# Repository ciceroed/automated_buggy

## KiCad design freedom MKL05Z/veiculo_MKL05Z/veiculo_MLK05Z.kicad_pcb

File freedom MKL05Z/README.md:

# Interface shield

This shield was adapted to connect MKL05Z pins to the car's power board. Go to [Power Board](hhttps://github.com/xtarke/automated_buggy/tree/master/power_board) for more hardware information.

## Analog pins

| Analog input  | KL05Z pin  | Board label  | Signal |
| ------------- | -------- | ------------ | ------ |
| ADC0          | PTA8       |   ADC0       | Bat0   |
| ADC1          | PTB9       |   ADC1       | Bat1   |
| ADC2          | PTB8       |   ADC2       | Ampop1 |
| ADC3          | PTA0       |   ADC3       | Ampop2 |

## Ultrasonic sensor

| MK05Z Pin | Signal|
| ------- | ------|
| PTB10       | Echo0 |
| PTB7       | Trig0 |
| PTA11       | Echo1 |
| PTA10       | Trig1 |

## Motors

|MK05Z Pin | Signal|  Board label |
| ---------- | ------| ------------ |
| PTB6          | PWM1  |  M1          |
| PTA12          | PWM1N |  M1N         |
| PTA5         | PWM2  |  M2          |
| PTB5          | PWM2N |  M2N         |

## Speed econder

| MKL05Z Pin | Signal |  Board label |
| ----------- | ------ | ------------ |
| PTB0          | D0     | ENC0         |
| PTA6          | D1     | ENC1         |

## Optic sensor

| MKL05Z Pin | Signal | Board label |
| ----------- | ------ | ----------- |
| PTB4          | R_TCRT | R DIR       |
| PTB3        | L_TCRT | L ESQ       |

## UART

| MKL05Z Pin | Signal |
| ------- | ------ |
| TX      | TX     |
| RX      | RX     |

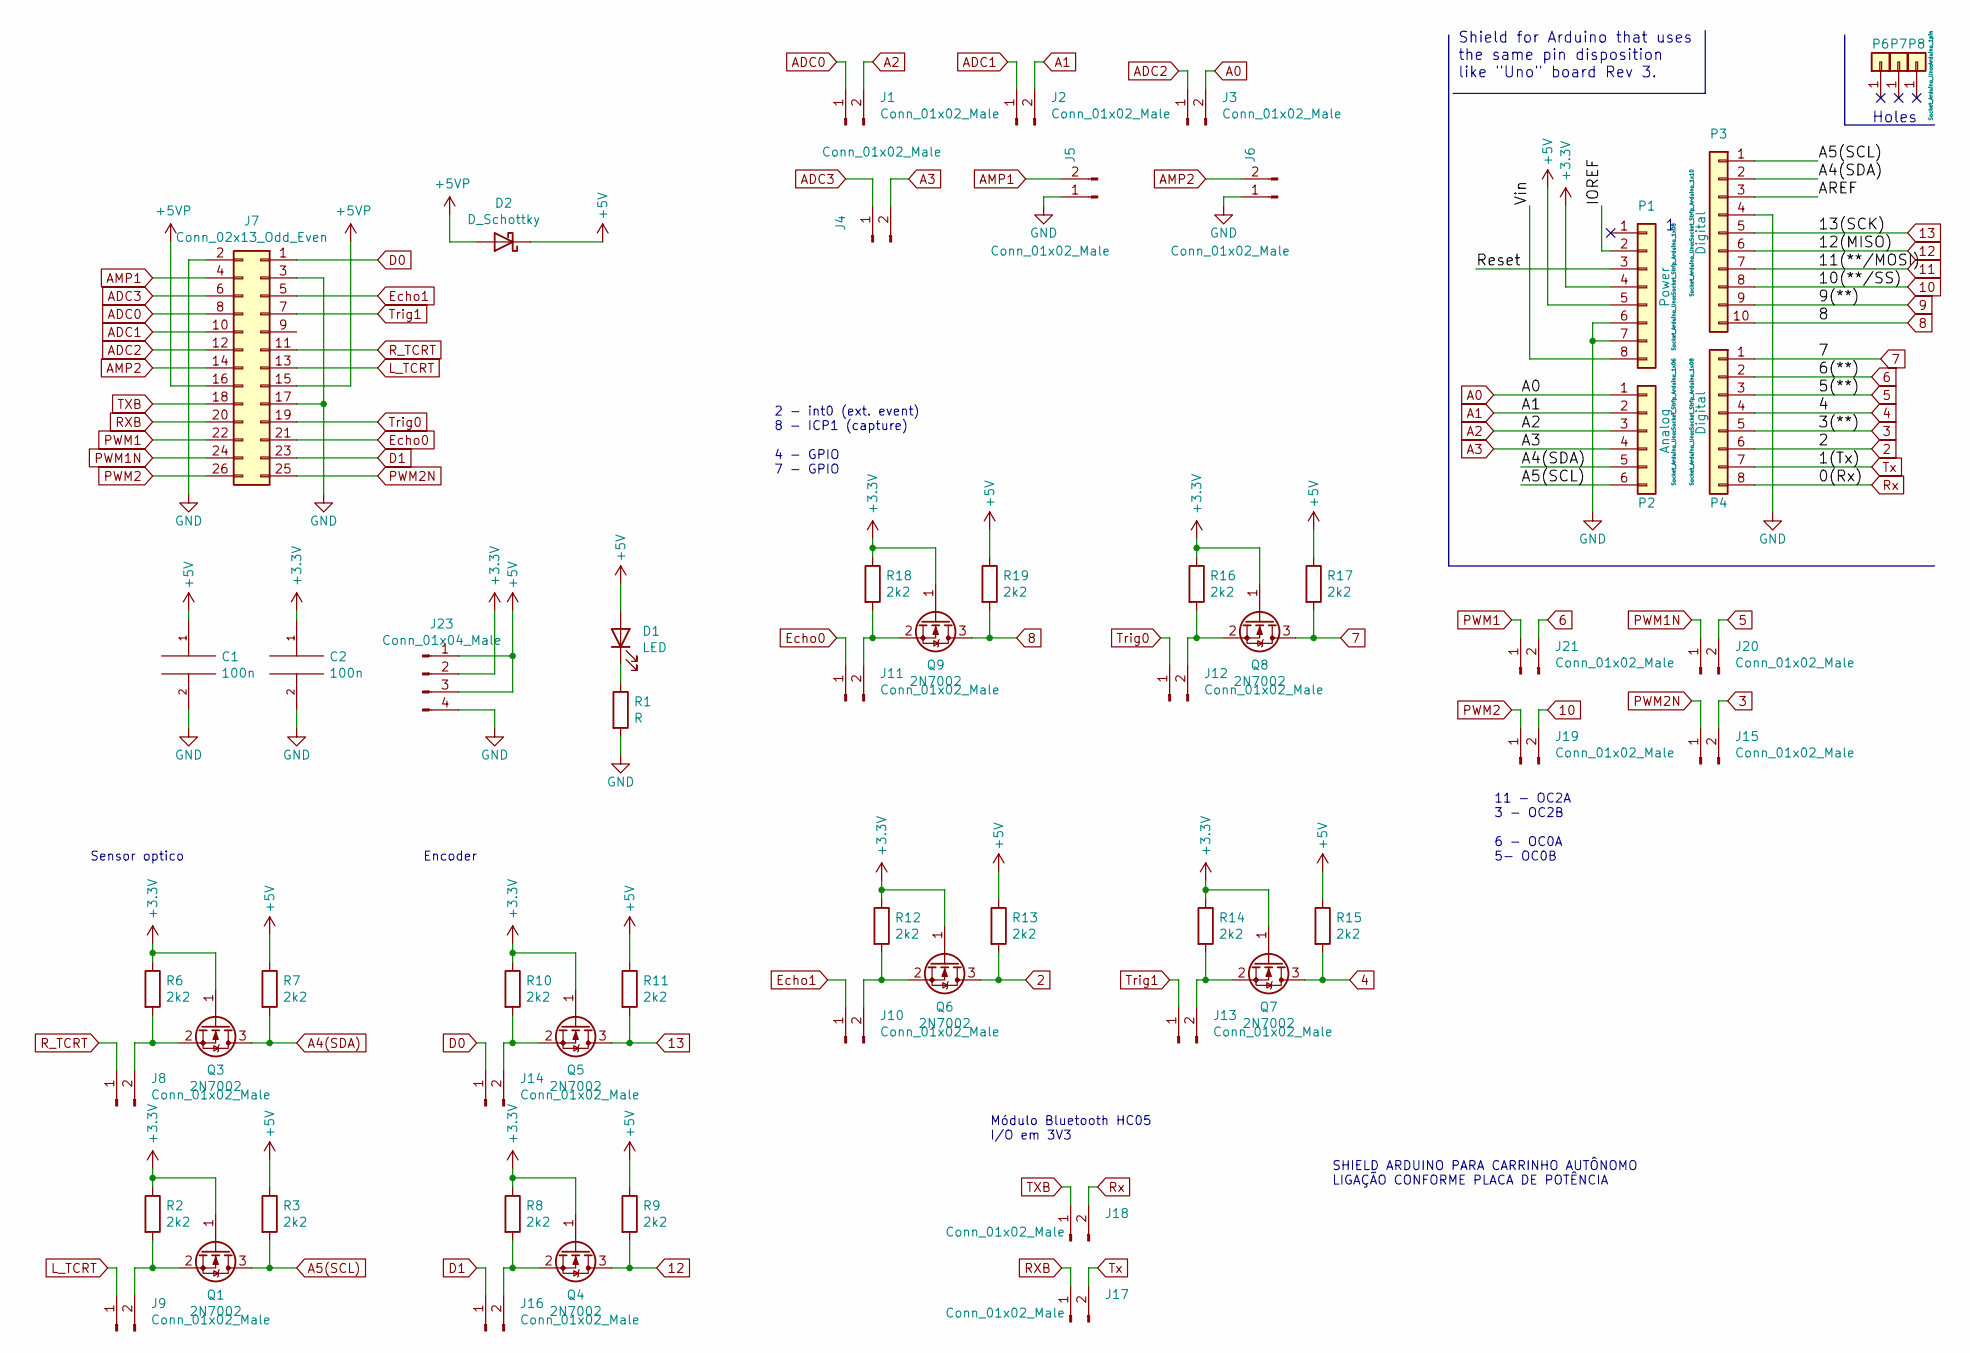
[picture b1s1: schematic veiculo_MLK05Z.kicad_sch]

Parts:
C1, C2: 100n; C_0805_2012Metric_Pad1.15x1.40mm_HandSolder
D1: LED; LED_0805_2012Metric
D2: D_Schottky; D_SMB
J1, J2, J3, J4, J5, J6, J8, J9, J10, J11, J12, J13, J14, J15, J16, J17, J18, J19, J20, J21: Conn_01x02_Male; PinHeader_1x02_P2.54mm_Vertical
J7: Conn_02x13_Odd_Even; IDC-Header_2x13_P2.54mm_Vertical
J23: Conn_01x04_Male; PinHeader_1x04_P2.54mm_Vertical
P1: Power; Socket_Strip_Arduino_1x08
P2: Analog; Socket_Strip_Arduino_1x06
P3: Digital; Socket_Strip_Arduino_1x10
P4: Digital; Socket_Strip_Arduino_1x08
P6, P7, P8: CONN_01X01; Arduino_1pin
Q1, Q3, Q4, Q5, Q6, Q7, Q8, Q9: 2N7002; SOT-23
R1: R; R_0805_2012Metric
R2, R3, R6, R7, R8, R9, R10, R11, R12, R13, R14, R15, R16, R17, R18, R19: 2k2; R_0805_2012Metric

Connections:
2: P4.6, Q6.3 (D), R13.2
3: J15.2, P4.5
4: P4.4, Q7.3 (D), R15.2
5: J20.2, P4.3
6: J21.2, P4.2
7: P4.1, Q8.3 (D), R17.2
8: P3.10, Q9.3 (D), R19.2
9: P3.9
10: J19.2, P3.8
11: P3.7
12: P3.6, Q4.3 (D), R9.2
13: P3.5, Q5.3 (D), R11.2
+3.3V: C2.1, J23.2, P1.4, Q1.1 (G), Q3.1 (G), Q4.1 (G), Q5.1 (G), Q6.1 (G), Q7.1 (G), Q8.1 (G), Q9.1 (G), R2.1, R6.1, R8.1, R10.1, R12.1, R14.1, R16.1, R18.1
+5V: C1.1, D1.2 (A), D2.1 (K), J23.1, J23.3, P1.5, R3.1, R7.1, R9.1, R11.1, R13.1, R15.1, R17.1, R19.1
+5VP: D2.2 (A), J7.15, J7.16
/AREF: P3.3
/IOREF: P1.2
/Reset: P1.3
/Vin: P1.8
A0: J3.2, P2.1
A1: J2.2, P2.2
A2: J1.2, P2.3
A3: J4.2, P2.4
A4(SDA): P2.5, P3.2, Q3.3 (D), R7.2
A5(SCL): P2.6, P3.1, Q1.3 (D), R3.2
ADC0: J1.1, J7.8
ADC1: J2.1, J7.10
ADC2: J3.1, J7.12
ADC3: J4.1, J7.6
AMP1: J5.2, J7.4
AMP2: J6.2, J7.14
D0: J7.1, J14.1
D1: J7.23, J16.1
Echo0: J7.21, J11.1
Echo1: J7.5, J10.1
GND: C1.2, C2.2, J5.1, J6.1, J7.2, J7.3, J7.17, J23.4, P1.6, P1.7, P3.4, R1.2
L_TCRT: J7.13, J9.1
unnamed: D1.1 (K), R1.1
unnamed: J8.2, Q3.2 (S), R6.2
unnamed: J9.2, Q1.2 (S), R2.2
unnamed: J10.2, Q6.2 (S), R12.2
unnamed: J11.2, Q9.2 (S), R18.2
unnamed: J12.2, Q8.2 (S), R16.2
unnamed: J13.2, Q7.2 (S), R14.2
unnamed: J14.2, Q5.2 (S), R10.2
unnamed: J16.2, Q4.2 (S), R8.2
PWM1: J7.22, J21.1
PWM1N: J7.24, J20.1
PWM2: J7.26, J19.1
PWM2N: J7.25, J15.1
RXB: J7.20, J17.1
R_TCRT: J7.11, J8.1
Rx: J18.2, P4.8
TXB: J7.18, J18.1
Trig0: J7.19, J12.1
Trig1: J7.7, J13.1
Tx: J17.2, P4.7

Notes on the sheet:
11 - OC2A 3 - OC2B 6 - OC0A 5- OC0B
Módulo Bluetooth HC05 I/O em 3V3
SHIELD ARDUINO PARA CARRINHO AUTÔNOMO LIGAÇÃO CONFORME PLACA DE POTÊNCIA
2 - int0 (ext. event) 8 - ICP1 (capture) 4 - GPIO 7 - GPIO
Encoder
Shield for Arduino that uses the same pin disposition like "Uno" board Rev 3.
Sensor optico
Holes

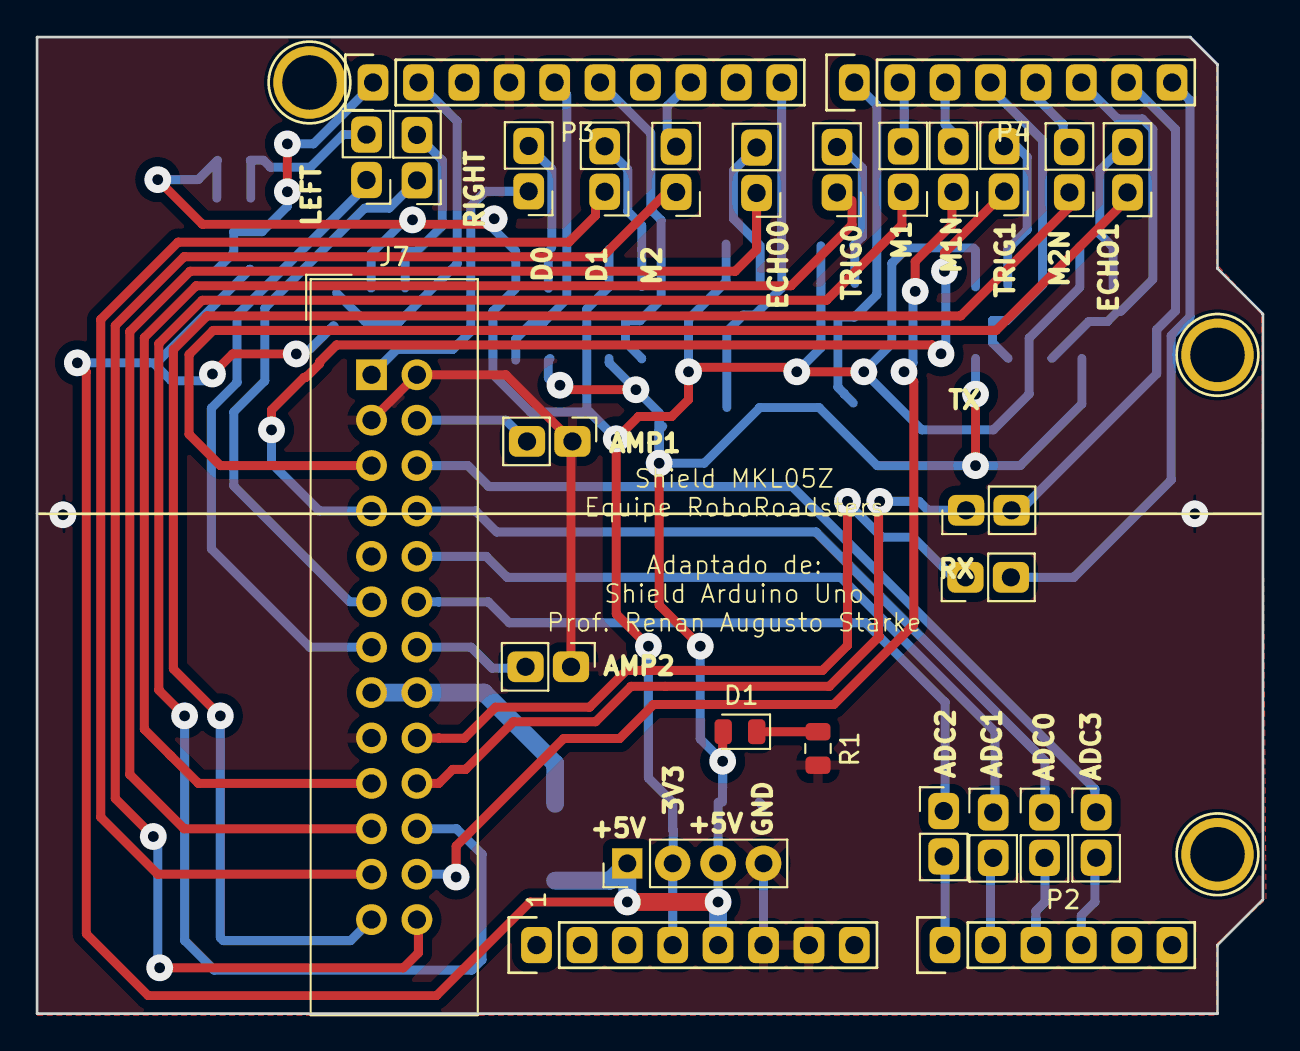
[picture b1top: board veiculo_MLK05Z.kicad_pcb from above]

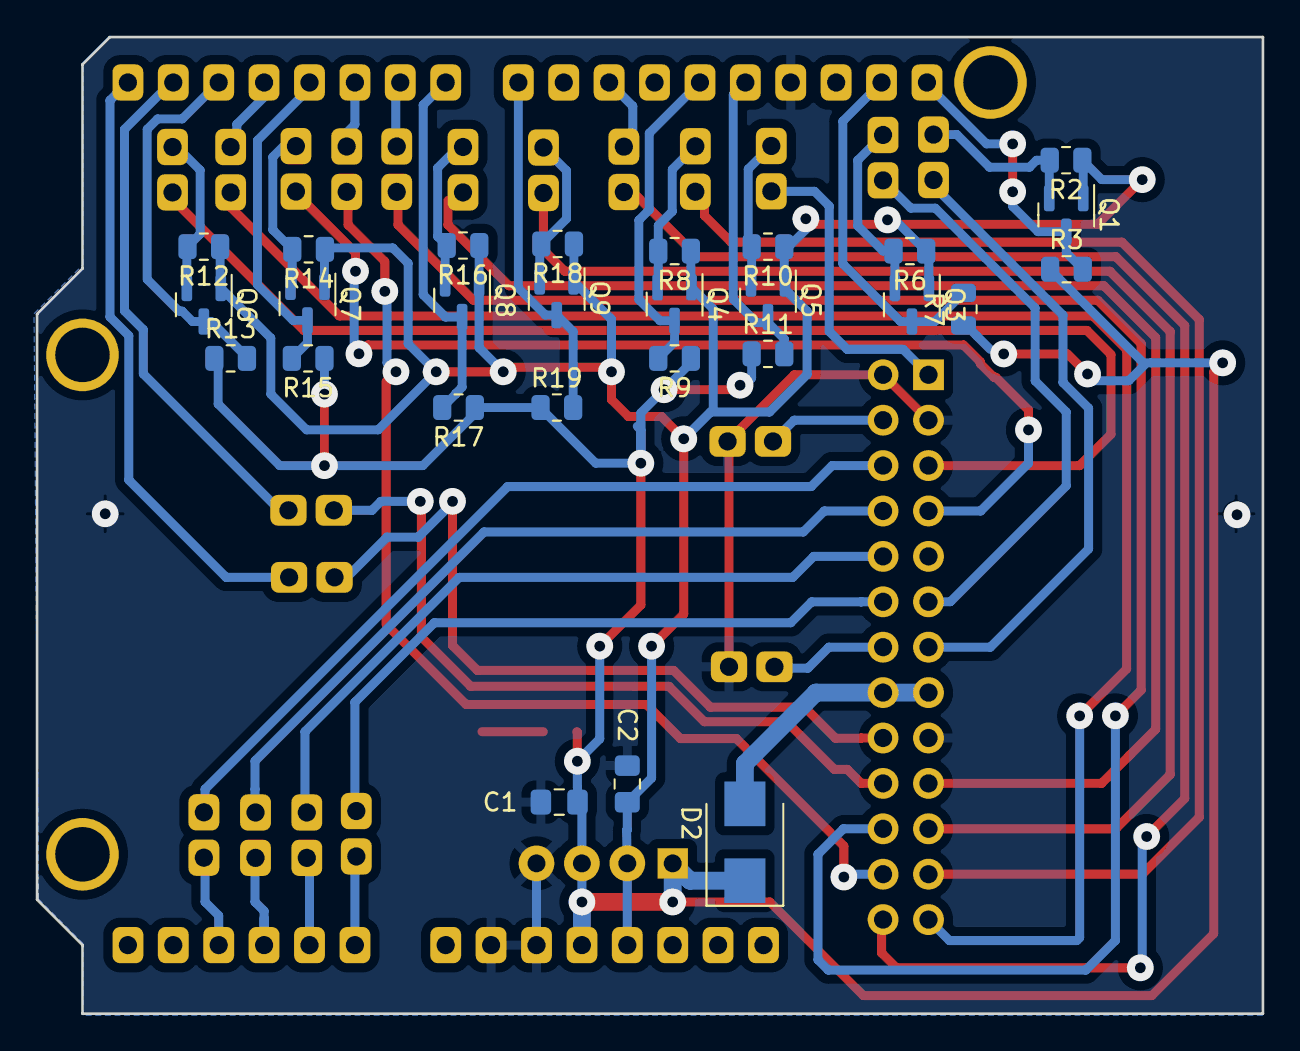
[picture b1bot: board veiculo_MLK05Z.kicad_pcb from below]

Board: 2 copper layers, 68.6 x 54.6 mm, 58 parts (27 on the bottom side), 51 nets.

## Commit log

2023-10-12 Update Files
2023-11-02 Created MKL05Z Shield
2023-11-02 Removed Unused Items
2023-11-04 Created README.md to MKL05Z Shield
2023-11-04 Update MKL05Z
2023-11-15 CNC Files
2023-11-20 cnc files update
